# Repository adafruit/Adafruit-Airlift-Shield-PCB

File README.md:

# Adafruit-Airlift-Shield-PCB
PCB files for the Adafruit Airlift Shield

Format is EagleCAD schematic and board layout

For more details, check out the product page at

   * https://www.adafruit.com/product/4285

Adafruit invests time and resources providing this open source design, 
please support Adafruit and open-source hardware by purchasing 
products from Adafruit!

Designed by Adafruit Industries.  
Creative Commons Attribution, Share-Alike license, check license.txt for more information
All text above must be included in any redistribution

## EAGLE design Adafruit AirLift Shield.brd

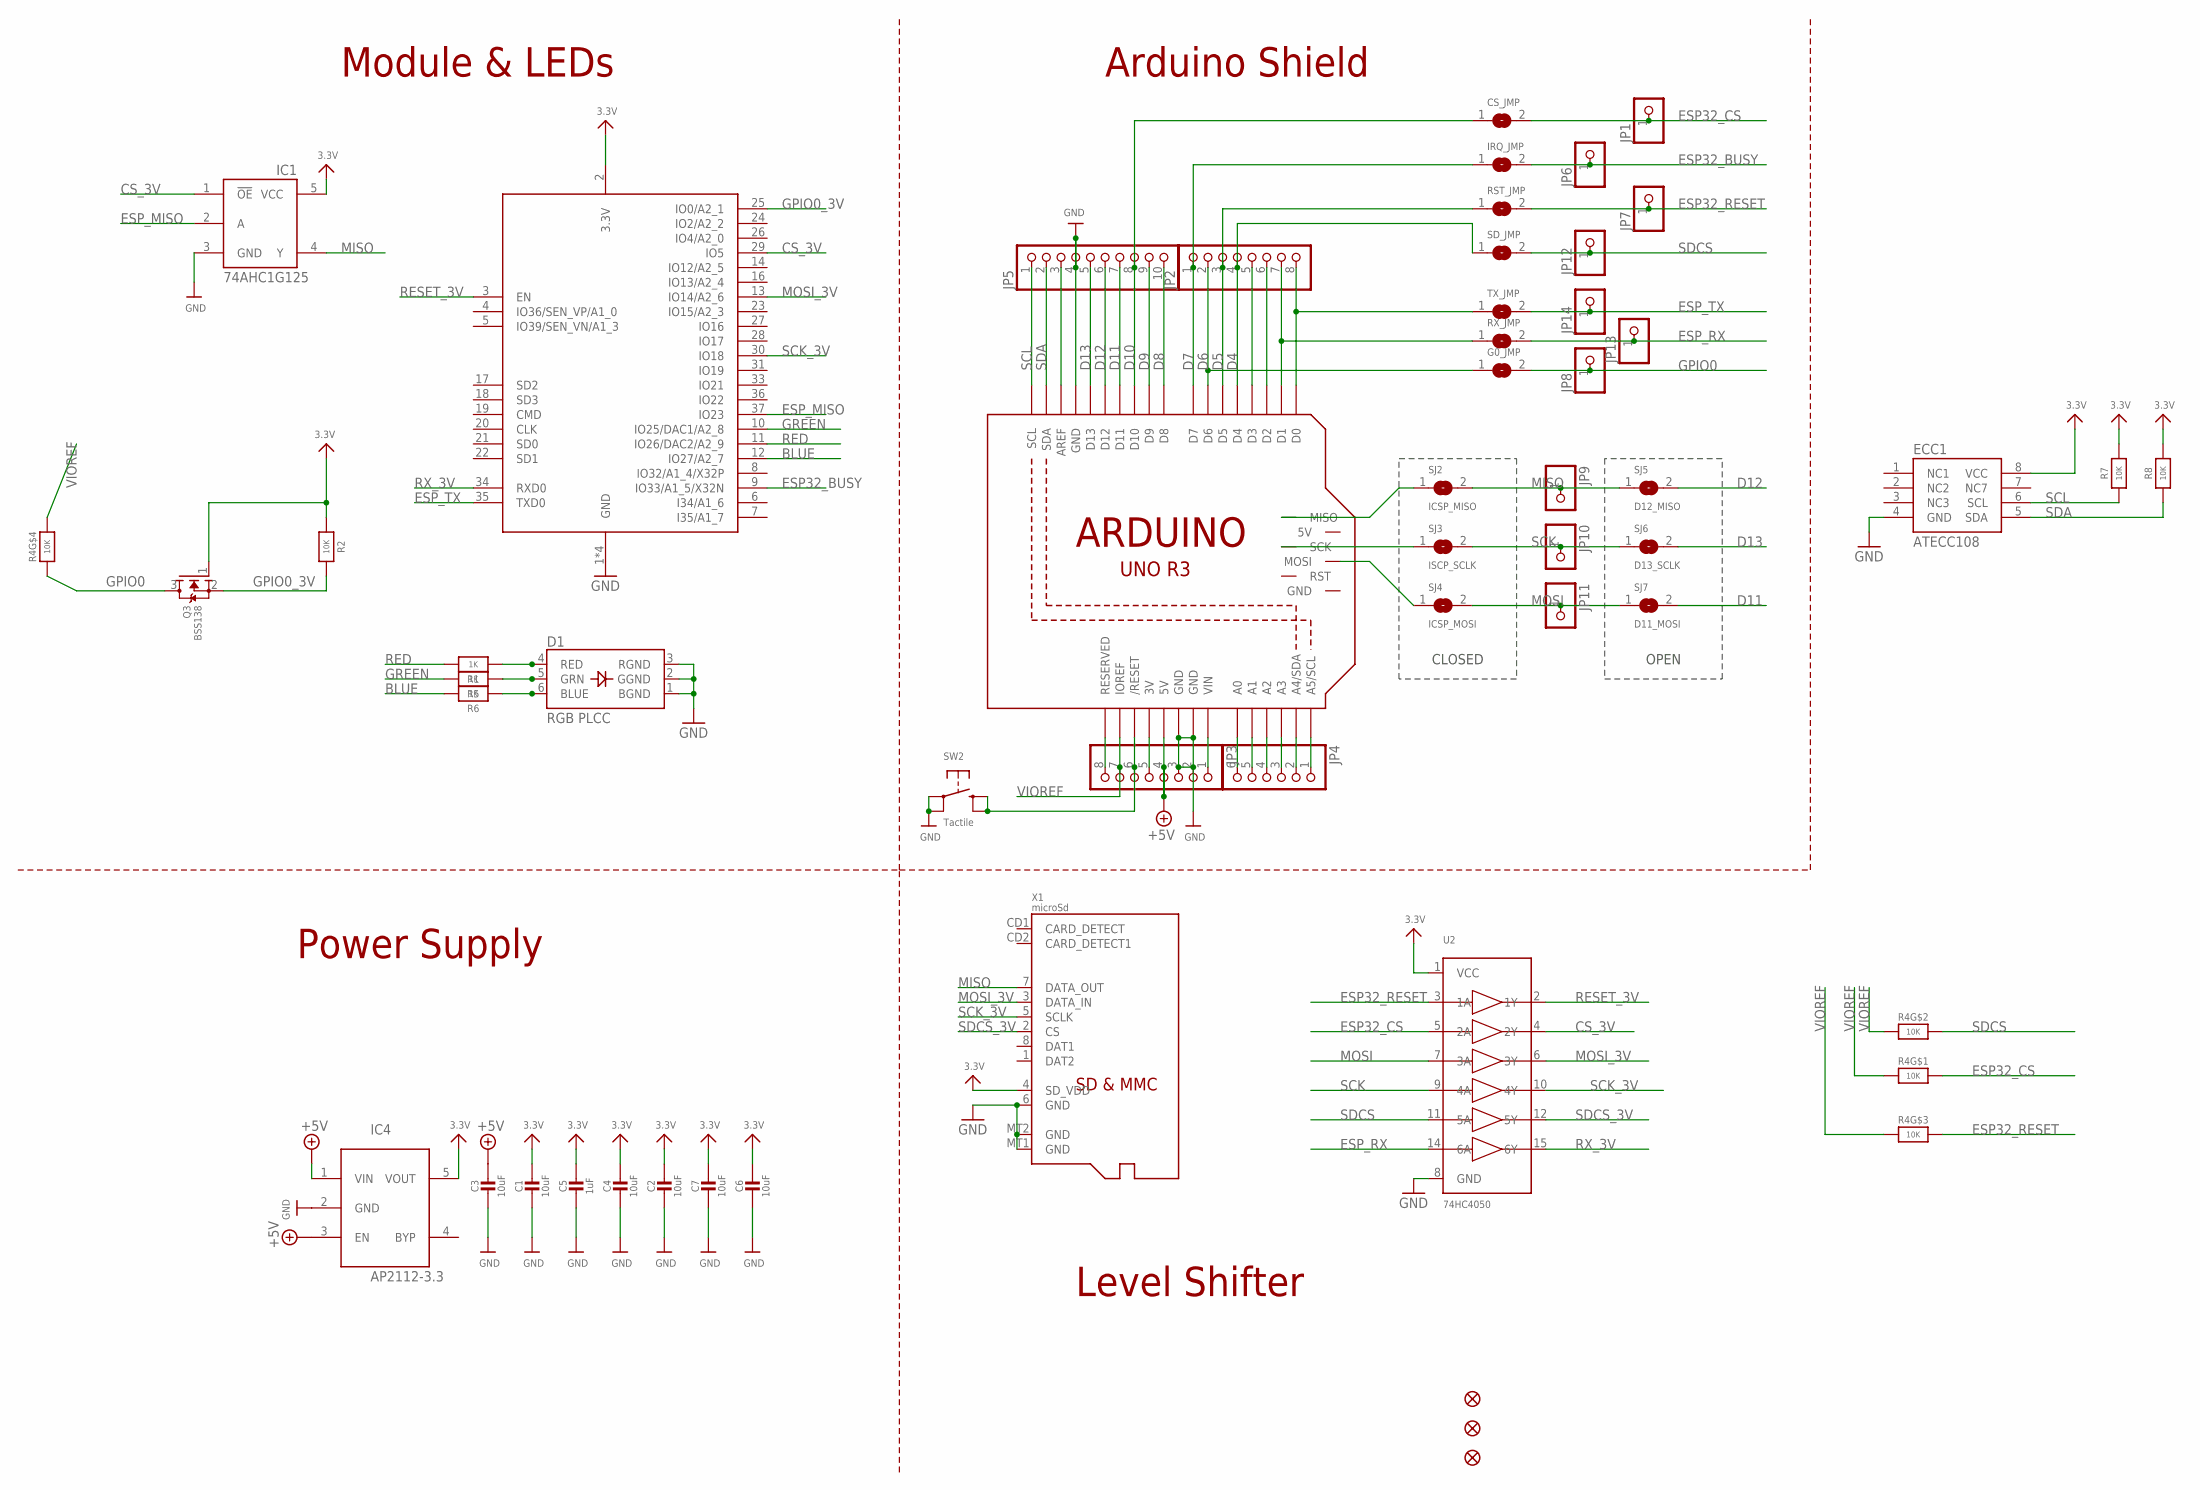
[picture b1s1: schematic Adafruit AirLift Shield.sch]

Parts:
C1, C2, C3, C4, C6, C7: 10uF; 0805-NO
C5: 1uF; 0805-NO
CS_JMP: SOLDERJUMPERCLOSED; SOLDERJUMPER_CLOSEDWIRE
D1: RGB PLCC; RGBLED_3535_PLCC6
ECC1: ATECC108; SOIC8
FID1, FID2, FID3: FIDUCIAL_1MM
G0_JMP: SOLDERJUMPER; SOLDERJUMPER_ARROW_NOPASTE
IC1: 74AHC1G125; SOT23-5L
IC4: AP2112-3.3; SOT23-5L
IRQ_JMP: SOLDERJUMPERCLOSED; SOLDERJUMPER_CLOSEDWIRE
JP1, JP6, JP7, JP8, JP9, JP10, JP11, JP12, JP13, JP14: HEADER-1X1ROUND; 1X01_ROUND
JP2, JP3: HEADER-1X870MIL; 1X08_ROUND_70
JP4: HEADER-1X670MIL; 1X06_ROUND_70
JP5: HEADER-1X1070MIL; 1X10_ROUND70
M1: ARDUINO_R3_ICSP_NODIM; ARDUINOR3_ICSP_NODIM
Q3: BSS138; SOT23-WIDE
R1, R5, R6: 1K; 0603-NO
R2, R7, R8: 10K; 0603-NO
R4: 10K; RESPACK_4X0603
RST_JMP: SOLDERJUMPERCLOSED; SOLDERJUMPER_CLOSEDWIRE
RX_JMP: SOLDERJUMPER; SOLDERJUMPER_ARROW_NOPASTE
SD_JMP: SOLDERJUMPERCLOSED; SOLDERJUMPER_CLOSEDWIRE
SJ2: ICSP_MISO; SOLDERJUMPER_CLOSEDWIRE
SJ3: ISCP_SCLK; SOLDERJUMPER_CLOSEDWIRE
SJ4: ICSP_MOSI; SOLDERJUMPER_CLOSEDWIRE
SJ5: D12_MISO; SOLDERJUMPER_REFLOW_NOPASTE
SJ6: D13_SCLK; SOLDERJUMPER_REFLOW_NOPASTE
SJ7: D11_MOSI; SOLDERJUMPER_REFLOW_NOPASTE
SW2: Tactile; EVQ-Q2_SMALLER
TX_JMP: SOLDERJUMPER; SOLDERJUMPER_ARROW_NOPASTE
U2: 74HC4050; SOIC16
X1: microSd; MICROSD
X2: ESP32_WROOM32; WROOM32

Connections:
3.3V: C1.1, C2.1, C4.1, C5.1, C6.1, C7.1, ECC1.8 (VCC), IC1.5 (VCC), IC4.5 (VOUT), Q3.1 (G), R2.1, R7.2, R8.2, U2.1 (VCC), X1.4 (SD_VDD), X2.2 (3.3V)
+3V: JP3.5, M1.3V
+5V: C3.1, IC4.1 (VIN), IC4.3 (EN), JP3.4, M1.5V
A0: JP4.6, M1.A0
A1: JP4.5, M1.A1
A2: JP4.4, M1.A2
A3: JP4.3, M1.A3
A4: JP4.2, M1.A4 (A4/SDA)
A5: JP4.1, M1.A5 (A5/SCL)
AREF: JP5.3, M1.AREF
BLUE: R6.2, X2.12 (IO27/A2_7)
CS_3V: IC1.1 (!OE), U2.4 (2Y), X2.29 (IO5)
D0: JP2.8, M1.D0, TX_JMP.1
D1: JP2.7, M1.D1, RX_JMP.1
D2: JP2.6, M1.D2
D3: JP2.5, M1.D3
D4: JP2.4, M1.D4, SD_JMP.1
D5: JP2.3, M1.D5, RST_JMP.1
D6: G0_JMP.1, JP2.2, M1.D6
D7: IRQ_JMP.1, JP2.1, M1.D7
D8: JP5.10, M1.D8
D9: JP5.9, M1.D9
D10: CS_JMP.1, JP5.8, M1.D10
D11: JP5.7, M1.D11, SJ7.2
D12: JP5.6, M1.D12, SJ5.2
D13: JP5.5, M1.D13, SJ6.2
ESP32_BUSY: IRQ_JMP.2, JP6.1, X2.9 (IO33/A1_5/X32N)
ESP32_CS: CS_JMP.2, JP1.1, R4.8 (2), U2.5 (2A)
ESP32_RESET: JP7.1, R4.6 (2), RST_JMP.2, U2.3 (1A)
ESP_MISO: IC1.2 (A), X2.37 (IO23)
ESP_RX: JP13.1, RX_JMP.2, U2.14 (6A)
ESP_TX: JP14.1, TX_JMP.2, X2.35 (TXD0)
GND: C1.2, C2.2, C3.2, C4.2, C5.2, C6.2, C7.2, D1.1 (BGND), D1.2 (GGND), D1.3 (RGND), ECC1.4 (GND), IC1.3 (GND), IC4.2 (GND), JP3.2, JP3.3, JP5.4, M1.GND, M1.GND@1 (GND), M1.GND@3 (GND), SW2.A, SW2.A' (P1), U2.8 (GND), X1.6 (GND), X1.MT1 (GND), X1.MT2 (GND), X2.1 (GND), X2.15 (GND), X2.38 (GND), X2.P$1 (GND)
GPIO0: G0_JMP.2, JP8.1, Q3.3 (D), R4.4 (1)
GPIO0_3V: Q3.2 (S), R2.2, X2.25 (IO0/A2_1)
GREEN: R5.2, X2.10 (IO25/DAC1/A2_8)
MISO: IC1.4 (Y), JP9.1, SJ2.2, SJ5.1, X1.7 (DATA_OUT)
MISO_ICSP: M1.MISO, SJ2.1
MOSI: JP11.1, SJ4.2, SJ7.1, U2.7 (3A)
MOSI_3V: U2.6 (3Y), X1.3 (DATA_IN), X2.13 (IO14/A2_6)
MOSI_ICSP: M1.MOSI, SJ4.1
unnamed: D1.4 (RED), R1.1
unnamed: D1.5 (GRN), R5.1
unnamed: D1.6 (BLUE), R6.1
NC: JP3.8, M1.RESERVED
RED: R1.2, X2.11 (IO26/DAC2/A2_9)
RESET: JP3.6, M1.RESET (/RESET), SW2.B (S), SW2.B' (S1)
RESET_3V: U2.2 (1Y), X2.3 (EN)
RX_3V: U2.15 (6Y), X2.34 (RXD0)
SCK: JP10.1, SJ3.2, SJ6.1, U2.9 (4A)
SCK_3V: U2.10 (4Y), X1.5 (SCLK), X2.30 (IO18)
SCK_ICSP: M1.SCK, SJ3.1
SCL: ECC1.6 (SCL), JP5.1, M1.SCL, R7.1
SDA: ECC1.5 (SDA), JP5.2, M1.SDA, R8.1
SDCS: JP12.1, R4.7 (2), SD_JMP.2, U2.11 (5A)
SDCS_3V: U2.12 (5Y), X1.2 (CS)
VIN: JP3.1, M1.VIN
VIOREF: JP3.7, M1.IOREF, R4.1, R4.2 (1), R4.3 (1), R4.5 (2)

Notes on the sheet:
CLOSED
OPEN
Module & LEDs
Level Shifter
Power Supply
Arduino Shield

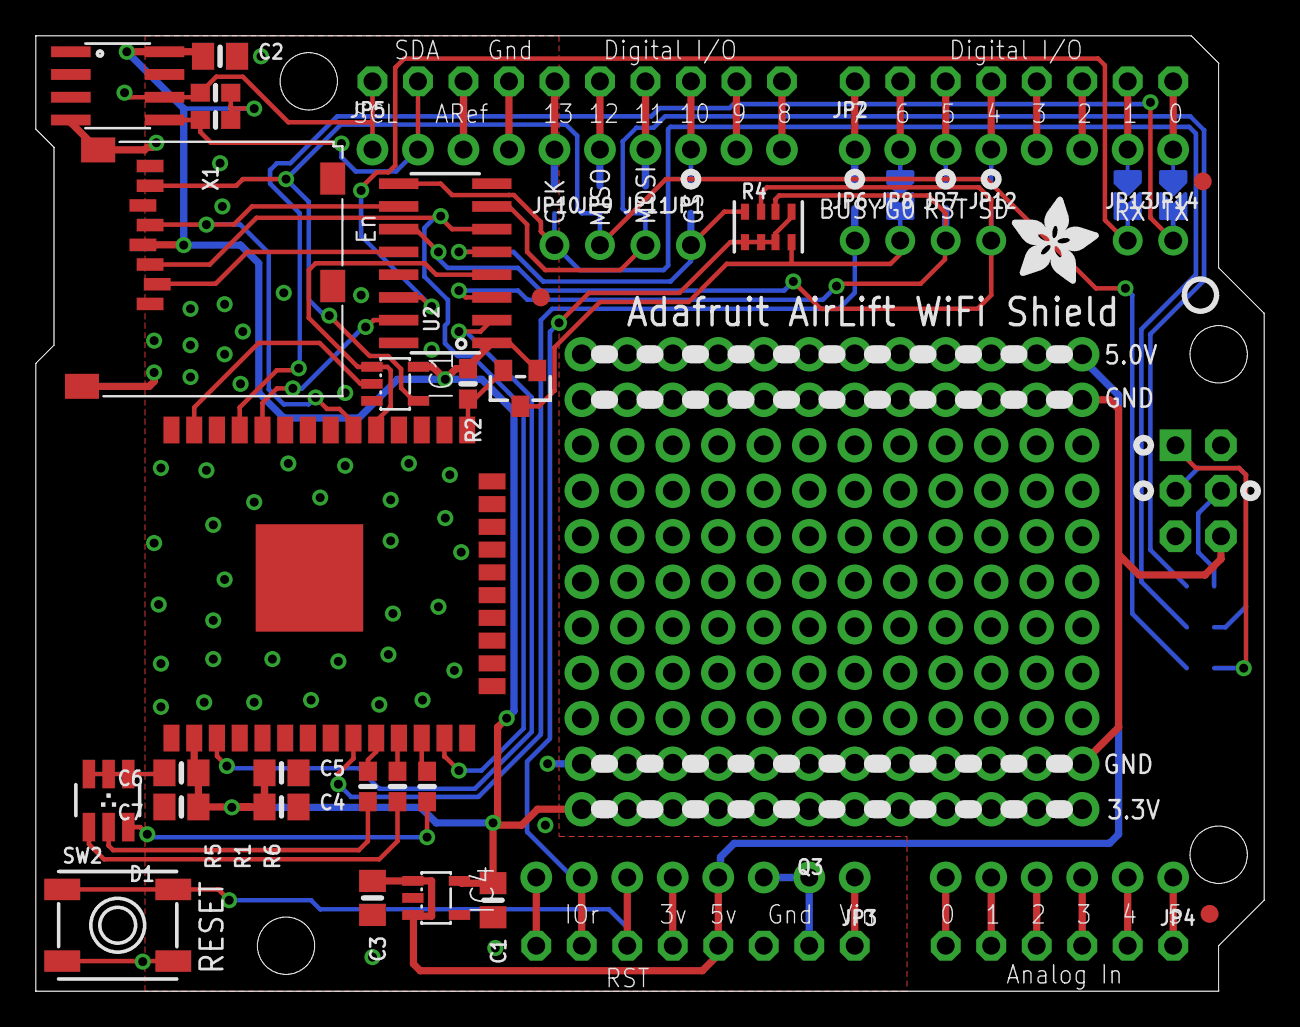
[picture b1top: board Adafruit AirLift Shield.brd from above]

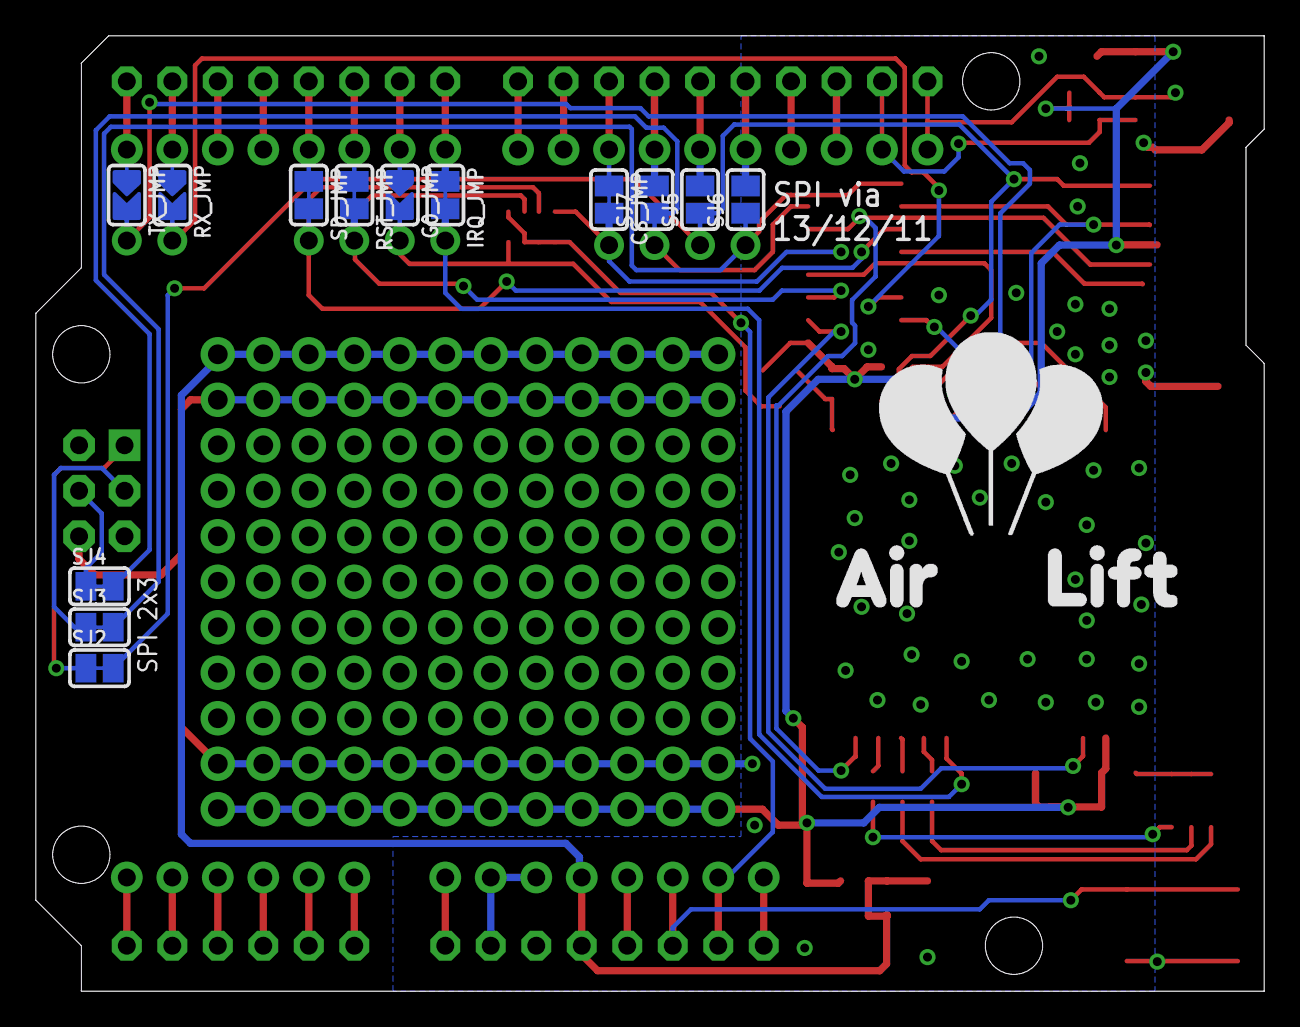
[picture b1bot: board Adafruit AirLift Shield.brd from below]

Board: 2 copper layers, 68.6 x 53.3 mm, 57 parts (14 on the bottom side), 58 nets.

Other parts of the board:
U$9: ADAFRUIT_5MM
U$21: PCBFEAT-REV-040
U$23: AIRLIFT

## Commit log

2019-06-20 Adding PCB Files

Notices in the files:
parts and their libraries:
microbuilder: This work is placed in the public domain, and may be freely used for commercial and non-commercial work with the following conditions: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
SparkFun-Aesthetics: Licensing: CC v3.0 Share-Alike You are welcome to use this library for commercial purposes.
